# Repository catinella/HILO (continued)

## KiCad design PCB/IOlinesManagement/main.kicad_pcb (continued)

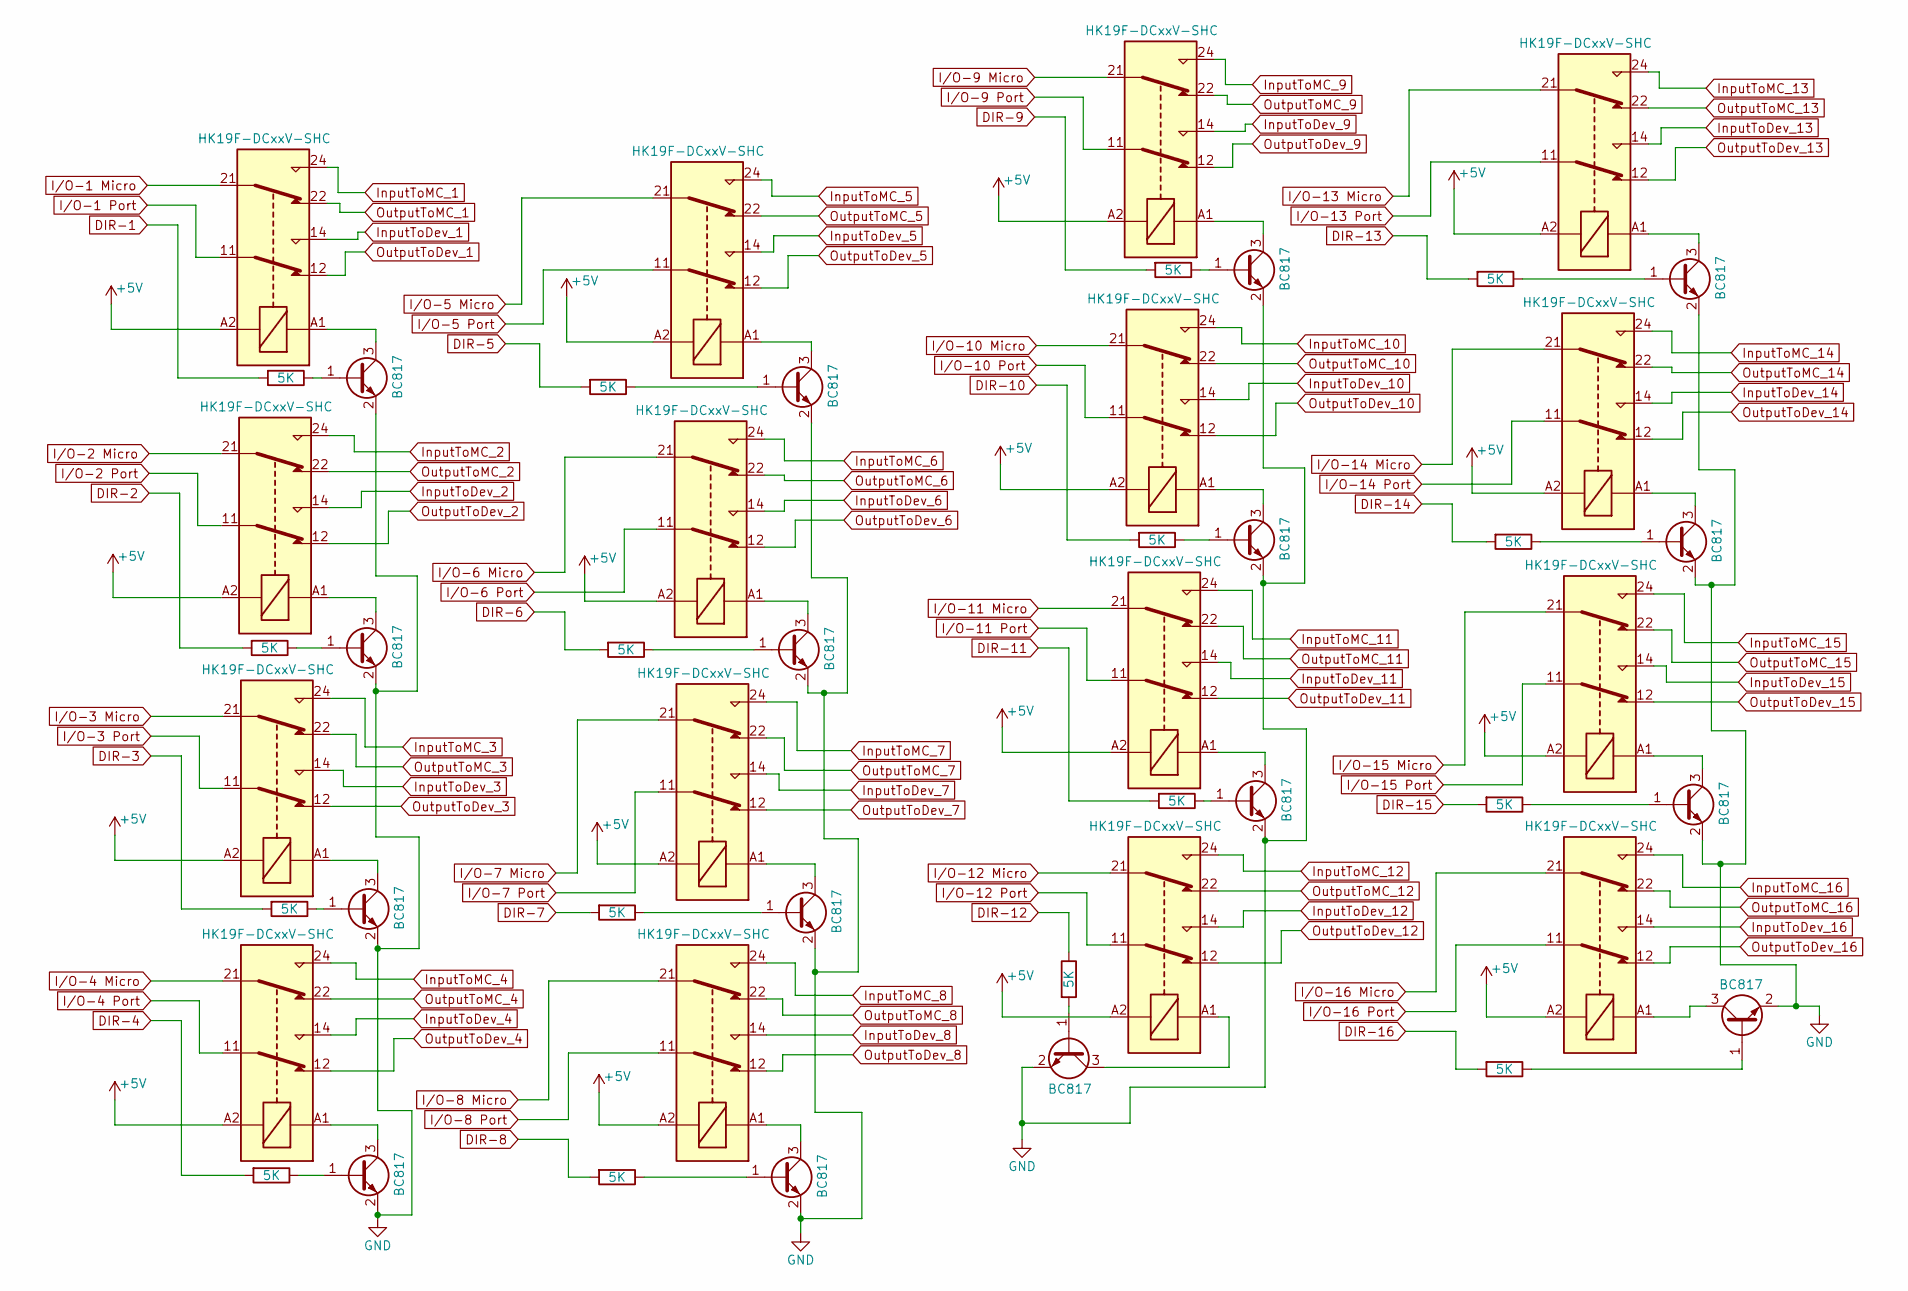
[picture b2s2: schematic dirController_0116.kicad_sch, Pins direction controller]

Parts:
K1, K2, K3, K4, K5, K6, K7, K8, K9, K10, K11, K12, K13, K14, K15, K16: HK19F-DCxxV-SHC; Relay_DPDT_Finder_30.22
Q1, Q2, Q3, Q4, Q5, Q6, Q7, Q8, Q9, Q10, Q11, Q12, Q13, Q14, Q15, Q16: BC817; SOT-23
R1, R2, R3, R4, R5, R6, R7, R8, R9, R10, R11, R12, R13, R14, R15, R16: 5K; R_1206_3216Metric

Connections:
+5V: K1.A2, K2.A2, K3.A2, K4.A2, K5.A2, K6.A2, K7.A2, K8.A2, K9.A2, K10.A2, K11.A2, K12.A2, K13.A2, K14.A2, K15.A2, K16.A2; also elsewhere on the board
DIR-1: R3.2; also elsewhere on the board
DIR-2: R1.2; also elsewhere on the board
DIR-3: R4.2; also elsewhere on the board
DIR-4: R2.2; also elsewhere on the board
DIR-5: R5.2; also elsewhere on the board
DIR-6: R8.2; also elsewhere on the board
DIR-7: R6.2; also elsewhere on the board
DIR-8: R7.2; also elsewhere on the board
DIR-9: R11.2; also elsewhere on the board
DIR-10: R10.2; also elsewhere on the board
DIR-11: R12.2; also elsewhere on the board
DIR-12: R9.1; also elsewhere on the board
DIR-13: R13.2; also elsewhere on the board
DIR-14: R16.2; also elsewhere on the board
DIR-15: R14.2; also elsewhere on the board
DIR-16: R15.2; also elsewhere on the board
GND: Q1.2 (E), Q2.2 (E), Q3.2 (E), Q4.2 (E), Q5.2 (E), Q6.2 (E), Q7.2 (E), Q8.2 (E), Q9.2 (E), Q10.2 (E), Q11.2 (E), Q12.2 (E), Q13.2 (E), Q14.2 (E), Q15.2 (E), Q16.2 (E); also elsewhere on the board
InputToDev_1: K1.14; also elsewhere on the board
InputToDev_2: K2.14; also elsewhere on the board
InputToDev_3: K3.14; also elsewhere on the board
InputToDev_4: K4.14; also elsewhere on the board
InputToDev_5: K5.14; also elsewhere on the board
InputToDev_6: K6.14; also elsewhere on the board
InputToDev_7: K7.14; also elsewhere on the board
InputToDev_8: K8.14; also elsewhere on the board
InputToDev_9: K9.14; also elsewhere on the board
InputToDev_10: K10.14; also elsewhere on the board
InputToDev_11: K11.14; also elsewhere on the board
InputToDev_12: K12.14; also elsewhere on the board
InputToDev_13: K13.14; also elsewhere on the board
InputToDev_14: K14.14; also elsewhere on the board
InputToDev_15: K15.14; also elsewhere on the board
InputToDev_16: K16.14; also elsewhere on the board
InputToMC_1: K1.24; also elsewhere on the board
InputToMC_2: K2.24; also elsewhere on the board
InputToMC_3: K3.24; also elsewhere on the board
InputToMC_4: K4.24; also elsewhere on the board
InputToMC_5: K5.24; also elsewhere on the board
InputToMC_6: K6.24; also elsewhere on the board
InputToMC_7: K7.24; also elsewhere on the board
InputToMC_8: K8.24; also elsewhere on the board
InputToMC_9: K9.24; also elsewhere on the board
InputToMC_10: K10.24; also elsewhere on the board
InputToMC_11: K11.24; also elsewhere on the board
InputToMC_12: K12.24; also elsewhere on the board
InputToMC_13: K13.24; also elsewhere on the board
InputToMC_14: K14.24; also elsewhere on the board
InputToMC_15: K15.24; also elsewhere on the board
InputToMC_16: K16.24; also elsewhere on the board
I/O-1 Micro: K1.21; also elsewhere on the board
I/O-1 Port: K1.11; also elsewhere on the board
I/O-2 Micro: K2.21; also elsewhere on the board
I/O-2 Port: K2.11; also elsewhere on the board
I/O-3 Micro: K3.21; also elsewhere on the board
I/O-3 Port: K3.11; also elsewhere on the board
I/O-4 Micro: K4.21; also elsewhere on the board
I/O-4 Port: K4.11; also elsewhere on the board
I/O-5 Micro: K5.21; also elsewhere on the board
I/O-5 Port: K5.11; also elsewhere on the board
I/O-6 Micro: K6.21; also elsewhere on the board
I/O-6 Port: K6.11; also elsewhere on the board
I/O-7 Micro: K7.21; also elsewhere on the board
I/O-7 Port: K7.11; also elsewhere on the board
I/O-8 Micro: K8.21; also elsewhere on the board
I/O-8 Port: K8.11; also elsewhere on the board
I/O-9 Micro: K9.21; also elsewhere on the board
I/O-9 Port: K9.11; also elsewhere on the board
I/O-10 Micro: K10.21; also elsewhere on the board
I/O-10 Port: K10.11; also elsewhere on the board
I/O-11 Micro: K11.21; also elsewhere on the board
I/O-11 Port: K11.11; also elsewhere on the board
I/O-12 Micro: K12.21; also elsewhere on the board
I/O-12 Port: K12.11; also elsewhere on the board
I/O-13 Micro: K13.21; also elsewhere on the board
I/O-13 Port: K13.11; also elsewhere on the board
I/O-14 Micro: K14.21; also elsewhere on the board
I/O-14 Port: K14.11; also elsewhere on the board
I/O-15 Micro: K15.21; also elsewhere on the board
I/O-15 Port: K15.11; also elsewhere on the board
I/O-16 Micro: K16.21; also elsewhere on the board
I/O-16 Port: K16.11; also elsewhere on the board
unnamed: Q1.1 (B), R3.1
unnamed: K1.A1, Q1.3 (C)
unnamed: Q2.1 (B), R1.1
unnamed: K2.A1, Q2.3 (C)
unnamed: Q3.1 (B), R4.1
unnamed: K3.A1, Q3.3 (C)
unnamed: Q4.1 (B), R2.1
unnamed: K4.A1, Q4.3 (C)
unnamed: Q5.1 (B), R7.1
unnamed: K8.A1, Q5.3 (C)
unnamed: Q6.1 (B), R8.1
unnamed: K6.A1, Q6.3 (C)
unnamed: Q7.1 (B), R5.1
unnamed: K5.A1, Q7.3 (C)
unnamed: Q8.1 (B), R6.1
unnamed: K7.A1, Q8.3 (C)
unnamed: Q9.1 (B), R9.2
unnamed: K12.A1, Q9.3 (C)
unnamed: Q10.1 (B), R11.1
unnamed: K9.A1, Q10.3 (C)
unnamed: Q11.1 (B), R10.1
unnamed: K10.A1, Q11.3 (C)
unnamed: Q12.1 (B), R12.1
unnamed: K11.A1, Q12.3 (C)
unnamed: Q13.1 (B), R16.1
unnamed: K14.A1, Q13.3 (C)
unnamed: Q14.1 (B), R13.1
unnamed: K13.A1, Q14.3 (C)
unnamed: Q15.1 (B), R14.1
unnamed: K15.A1, Q15.3 (C)
unnamed: Q16.1 (B), R15.1
unnamed: K16.A1, Q16.3 (C)
OutputToDev_1: K1.12; also elsewhere on the board
OutputToDev_2: K2.12; also elsewhere on the board
OutputToDev_3: K3.12; also elsewhere on the board
OutputToDev_4: K4.12; also elsewhere on the board
OutputToDev_5: K5.12; also elsewhere on the board
OutputToDev_6: K6.12; also elsewhere on the board
OutputToDev_7: K7.12; also elsewhere on the board
OutputToDev_8: K8.12; also elsewhere on the board
OutputToDev_9: K9.12; also elsewhere on the board
OutputToDev_10: K10.12; also elsewhere on the board
OutputToDev_11: K11.12; also elsewhere on the board
OutputToDev_12: K12.12; also elsewhere on the board
OutputToDev_13: K13.12; also elsewhere on the board
OutputToDev_14: K14.12; also elsewhere on the board
OutputToDev_15: K15.12; also elsewhere on the board
OutputToDev_16: K16.12; also elsewhere on the board
OutputToMC_1: K1.22; also elsewhere on the board
OutputToMC_2: K2.22; also elsewhere on the board
OutputToMC_3: K3.22; also elsewhere on the board
OutputToMC_4: K4.22; also elsewhere on the board
OutputToMC_5: K5.22; also elsewhere on the board
OutputToMC_6: K6.22; also elsewhere on the board
OutputToMC_7: K7.22; also elsewhere on the board
OutputToMC_8: K8.22; also elsewhere on the board
OutputToMC_9: K9.22; also elsewhere on the board
OutputToMC_10: K10.22; also elsewhere on the board
OutputToMC_11: K11.22; also elsewhere on the board
OutputToMC_12: K12.22; also elsewhere on the board
OutputToMC_13: K13.22; also elsewhere on the board
OutputToMC_14: K14.22; also elsewhere on the board
OutputToMC_15: K15.22; also elsewhere on the board
OutputToMC_16: K16.22; also elsewhere on the board

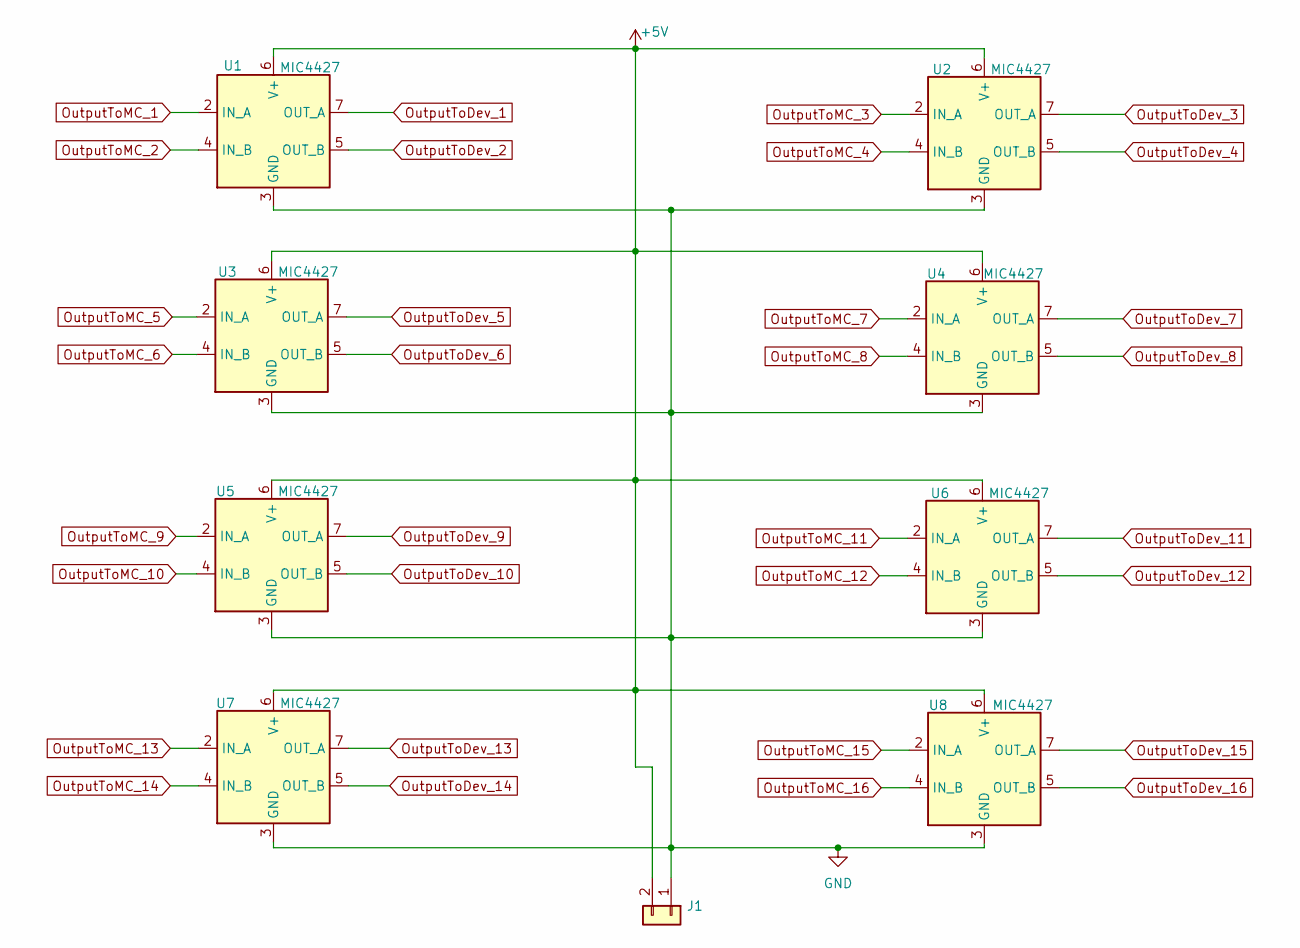
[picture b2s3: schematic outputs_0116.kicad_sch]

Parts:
J1: Conn_01x02; PinHeader_1x02_P2.54mm_Vertical
U1, U2, U3, U4, U5, U6, U7, U8: MIC4427; MSOP-8_3x3mm_P0.65mm

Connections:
+5V: J1.2, U1.6 (V+), U2.6 (V+), U3.6 (V+), U4.6 (V+), U5.6 (V+), U6.6 (V+), U7.6 (V+), U8.6 (V+); also elsewhere on the board
GND: J1.1, U1.3 (GND), U2.3 (GND), U3.3 (GND), U4.3 (GND), U5.3 (GND), U6.3 (GND), U7.3 (GND), U8.3 (GND); also elsewhere on the board
OutputToDev_1: U1.7 (OUT_A); also elsewhere on the board
OutputToDev_2: U1.5 (OUT_B); also elsewhere on the board
OutputToDev_3: U2.7 (OUT_A); also elsewhere on the board
OutputToDev_4: U2.5 (OUT_B); also elsewhere on the board
OutputToDev_5: U3.7 (OUT_A); also elsewhere on the board
OutputToDev_6: U3.5 (OUT_B); also elsewhere on the board
OutputToDev_7: U4.7 (OUT_A); also elsewhere on the board
OutputToDev_8: U4.5 (OUT_B); also elsewhere on the board
OutputToDev_9: U5.7 (OUT_A); also elsewhere on the board
OutputToDev_10: U5.5 (OUT_B); also elsewhere on the board
OutputToDev_11: U6.7 (OUT_A); also elsewhere on the board
OutputToDev_12: U6.5 (OUT_B); also elsewhere on the board
OutputToDev_13: U7.7 (OUT_A); also elsewhere on the board
OutputToDev_14: U7.5 (OUT_B); also elsewhere on the board
OutputToDev_15: U8.7 (OUT_A); also elsewhere on the board
OutputToDev_16: U8.5 (OUT_B); also elsewhere on the board
OutputToMC_1: U1.2 (IN_A); also elsewhere on the board
OutputToMC_2: U1.4 (IN_B); also elsewhere on the board
OutputToMC_3: U2.2 (IN_A); also elsewhere on the board
OutputToMC_4: U2.4 (IN_B); also elsewhere on the board
OutputToMC_5: U3.2 (IN_A); also elsewhere on the board
OutputToMC_6: U3.4 (IN_B); also elsewhere on the board
OutputToMC_7: U4.2 (IN_A); also elsewhere on the board
OutputToMC_8: U4.4 (IN_B); also elsewhere on the board
OutputToMC_9: U5.2 (IN_A); also elsewhere on the board
OutputToMC_10: U5.4 (IN_B); also elsewhere on the board
OutputToMC_11: U6.2 (IN_A); also elsewhere on the board
OutputToMC_12: U6.4 (IN_B); also elsewhere on the board
OutputToMC_13: U7.2 (IN_A); also elsewhere on the board
OutputToMC_14: U7.4 (IN_B); also elsewhere on the board
OutputToMC_15: U8.2 (IN_A); also elsewhere on the board
OutputToMC_16: U8.4 (IN_B); also elsewhere on the board

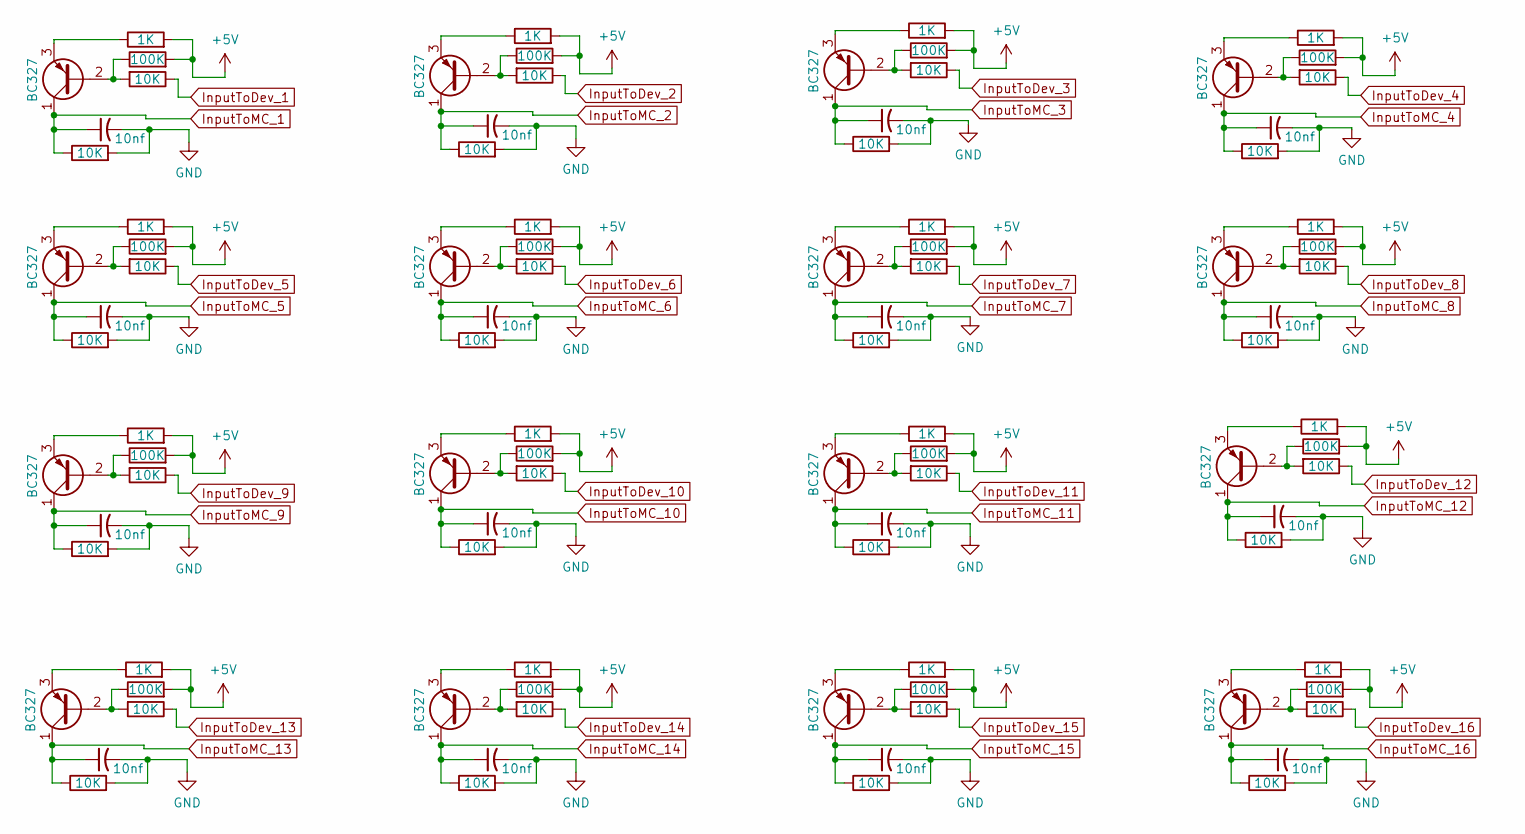
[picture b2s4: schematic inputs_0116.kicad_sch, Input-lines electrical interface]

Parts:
C1, C2, C3, C4, C5, C6, C7, C8, C9, C10, C11, C12, C13, C14, C15, C16: 10nf; C_Disc_D4.3mm_W1.9mm_P5.00mm
Q25, Q34, Q51, Q52, Q53, Q54, Q55, Q56, Q57, Q58, Q59, Q60, Q61, Q62, Q63, Q64: BC327; TO-92_Inline_Wide
R17, R54, R82, R112, R113, R114, R117, R120, R125, R128, R140, R146, R147, R148, R151, R156: 1K; R_1206_3216Metric
R40, R56, R65, R84, R105, R106, R107, R108, R109, R110, R111, R116, R119, R122, R124, R127, R130, R132, R133, R134, R135, R136, R137, R138, R139, R142, R145, R150, R153, R155, R158, R160: 10K; R_1206_3216Metric
R55, R83, R115, R118, R121, R123, R126, R129, R131, R141, R144, R149, R152, R154, R157, R159: 100K; R_1206_3216Metric

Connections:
+5V: R17.2, R54.2, R55.2, R82.2, R83.2, R112.2, R113.2, R114.2, R115.2, R117.2, R118.2, R120.2, R121.2, R123.2, R125.2, R126.2, R128.2, R129.2, R131.2, R140.2, R141.2, R144.2, R146.2, R147.2, R148.2, R149.2, R151.2, R152.2, R154.2, R156.2, R157.2, R159.2; also elsewhere on the board
GND: C1.2, C2.2, C3.2, C4.2, C5.2, C6.2, C7.2, C8.2, C9.2, C10.2, C11.2, C12.2, C13.2, C14.2, C15.2, C16.2, R40.2, R65.2, R105.2, R106.2, R107.2, R108.2, R109.2, R110.2, R111.2, R133.2, R134.2, R135.2, R136.2, R137.2, R138.2, R139.2; also elsewhere on the board
InputToDev_1: R56.1; also elsewhere on the board
InputToDev_2: R84.1; also elsewhere on the board
InputToDev_3: R142.1; also elsewhere on the board
InputToDev_4: R132.1; also elsewhere on the board
InputToDev_5: R122.1; also elsewhere on the board
InputToDev_6: R145.1; also elsewhere on the board
InputToDev_7: R153.1; also elsewhere on the board
InputToDev_8: R116.1; also elsewhere on the board
InputToDev_9: R124.1; also elsewhere on the board
InputToDev_10: R119.1; also elsewhere on the board
InputToDev_11: R130.1; also elsewhere on the board
InputToDev_12: R127.1; also elsewhere on the board
InputToDev_13: R155.1; also elsewhere on the board
InputToDev_14: R150.1; also elsewhere on the board
InputToDev_15: R160.1; also elsewhere on the board
InputToDev_16: R158.1; also elsewhere on the board
InputToMC_1: C1.1, Q25.1 (C), R40.1; also elsewhere on the board
InputToMC_2: C2.1, Q34.1 (C), R65.1; also elsewhere on the board
InputToMC_3: C10.1, Q58.1 (C), R133.1; also elsewhere on the board
InputToMC_4: C9.1, Q57.1 (C), R111.1; also elsewhere on the board
InputToMC_5: C5.1, Q53.1 (C), R107.1; also elsewhere on the board
InputToMC_6: C11.1, Q59.1 (C), R134.1; also elsewhere on the board
InputToMC_7: C13.1, Q61.1 (C), R136.1; also elsewhere on the board
InputToMC_8: C3.1, Q51.1 (C), R105.1; also elsewhere on the board
InputToMC_9: C6.1, Q54.1 (C), R108.1; also elsewhere on the board
InputToMC_10: C4.1, Q52.1 (C), R106.1; also elsewhere on the board
InputToMC_11: C8.1, Q56.1 (C), R110.1; also elsewhere on the board
InputToMC_12: C7.1, Q55.1 (C), R109.1; also elsewhere on the board
InputToMC_13: C14.1, Q62.1 (C), R137.1; also elsewhere on the board
InputToMC_14: C12.1, Q60.1 (C), R135.1; also elsewhere on the board
InputToMC_15: C16.1, Q64.1 (C), R139.1; also elsewhere on the board
InputToMC_16: C15.1, Q63.1 (C), R138.1; also elsewhere on the board
unnamed: Q25.2 (B), R55.1, R56.2
unnamed: Q25.3 (E), R54.1
unnamed: Q34.2 (B), R83.1, R84.2
unnamed: Q34.3 (E), R82.1
unnamed: Q51.2 (B), R115.1, R116.2
unnamed: Q51.3 (E), R112.1
unnamed: Q52.2 (B), R118.1, R119.2
unnamed: Q52.3 (E), R113.1
unnamed: Q53.2 (B), R121.1, R122.2
unnamed: Q53.3 (E), R114.1
unnamed: Q54.2 (B), R123.1, R124.2
unnamed: Q54.3 (E), R117.1
unnamed: Q55.2 (B), R126.1, R127.2
unnamed: Q55.3 (E), R120.1
unnamed: Q56.2 (B), R129.1, R130.2
unnamed: Q56.3 (E), R125.1
unnamed: Q57.2 (B), R131.1, R132.2
unnamed: Q57.3 (E), R128.1
unnamed: Q58.2 (B), R141.1, R142.2
unnamed: Q58.3 (E), R140.1
unnamed: Q59.2 (B), R144.1, R145.2
unnamed: Q59.3 (E), R17.1
unnamed: Q60.2 (B), R149.1, R150.2
unnamed: Q60.3 (E), R146.1
unnamed: Q61.2 (B), R152.1, R153.2
unnamed: Q61.3 (E), R147.1
unnamed: Q62.2 (B), R154.1, R155.2
unnamed: Q62.3 (E), R148.1
unnamed: Q63.2 (B), R157.1, R158.2
unnamed: Q63.3 (E), R151.1
unnamed: Q64.2 (B), R159.1, R160.2
unnamed: Q64.3 (E), R156.1

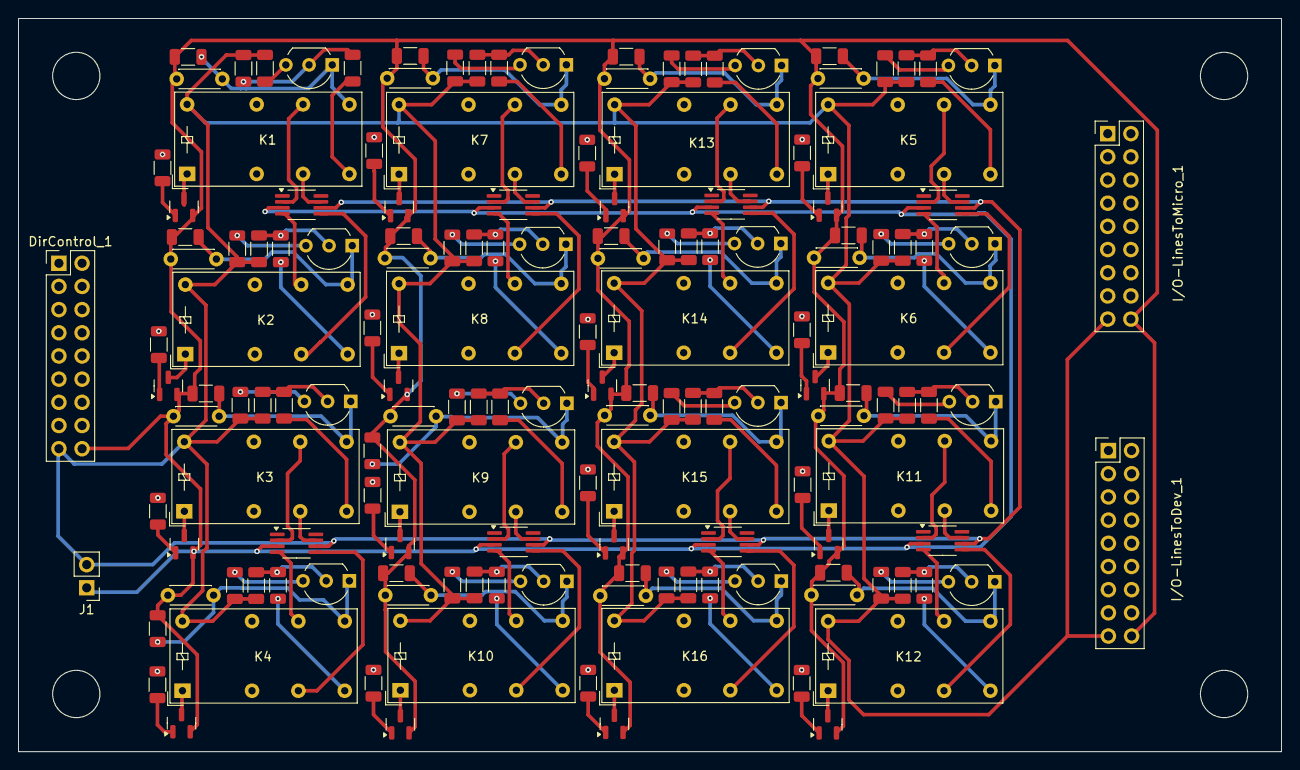
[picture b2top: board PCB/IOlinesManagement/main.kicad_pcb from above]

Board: 4 copper layers, 138.4 x 80.3 mm, 156 parts (0 on the bottom side), 178 nets.

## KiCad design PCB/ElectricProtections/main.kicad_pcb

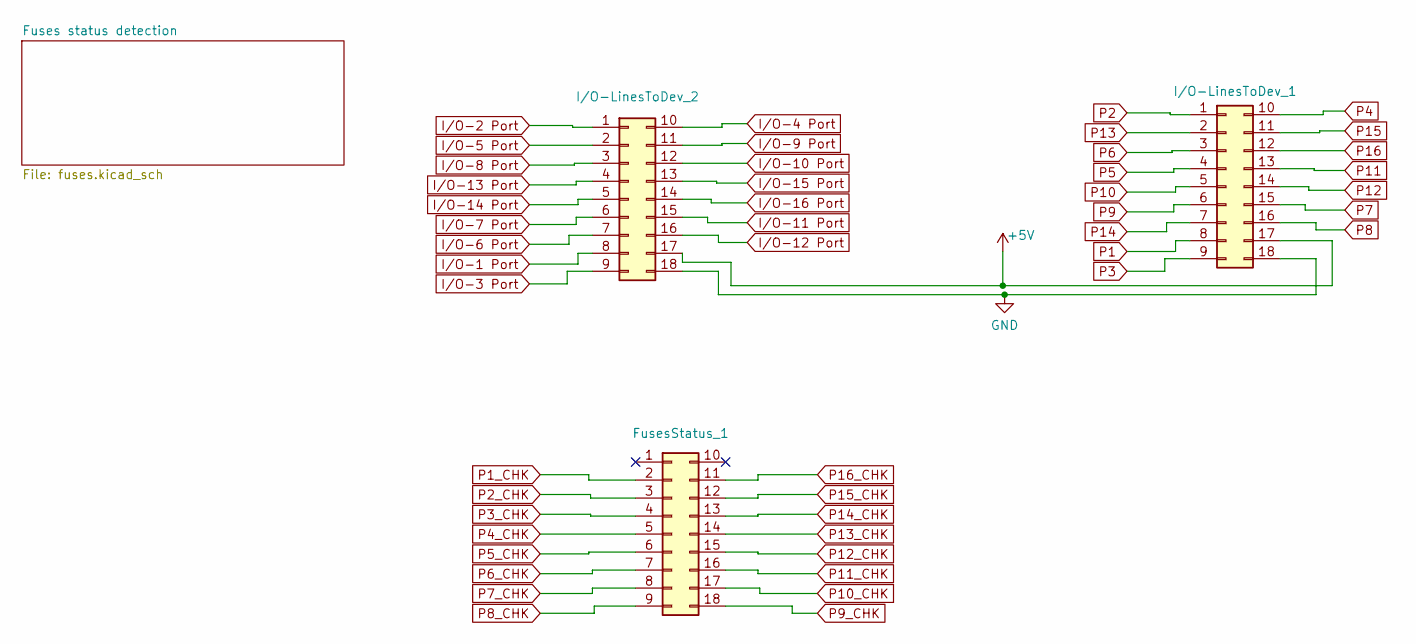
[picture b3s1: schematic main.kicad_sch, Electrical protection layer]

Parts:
FusesStatus_1: Conn_02x09_Top_Bottom; PinHeader_2x09_P2.54mm_Vertical
I/O-LinesToDev_1, I/O-LinesToDev_2: Conn_02x09_Top_Bottom; PinHeader_2x09_P2.54mm_Vertical

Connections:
+5V: I/O-LinesToDev_1.17, I/O-LinesToDev_2.17; also elsewhere on the board
GND: I/O-LinesToDev_1.18, I/O-LinesToDev_2.18; also elsewhere on the board
I/O-1 Port: I/O-LinesToDev_2.8; also elsewhere on the board
I/O-2 Port: I/O-LinesToDev_2.1; also elsewhere on the board
I/O-3 Port: I/O-LinesToDev_2.9; also elsewhere on the board
I/O-4 Port: I/O-LinesToDev_2.10; also elsewhere on the board
I/O-5 Port: I/O-LinesToDev_2.2; also elsewhere on the board
I/O-6 Port: I/O-LinesToDev_2.7; also elsewhere on the board
I/O-7 Port: I/O-LinesToDev_2.6; also elsewhere on the board
I/O-8 Port: I/O-LinesToDev_2.3; also elsewhere on the board
I/O-9 Port: I/O-LinesToDev_2.11; also elsewhere on the board
I/O-10 Port: I/O-LinesToDev_2.12; also elsewhere on the board
I/O-11 Port: I/O-LinesToDev_2.15; also elsewhere on the board
I/O-12 Port: I/O-LinesToDev_2.16; also elsewhere on the board
I/O-13 Port: I/O-LinesToDev_2.4; also elsewhere on the board
I/O-14 Port: I/O-LinesToDev_2.5; also elsewhere on the board
I/O-15 Port: I/O-LinesToDev_2.13; also elsewhere on the board
I/O-16 Port: I/O-LinesToDev_2.14; also elsewhere on the board
P1: I/O-LinesToDev_1.8; also elsewhere on the board
P1_CHK: FusesStatus_1.2; also elsewhere on the board
P2: I/O-LinesToDev_1.1; also elsewhere on the board
P2_CHK: FusesStatus_1.3; also elsewhere on the board
P3: I/O-LinesToDev_1.9; also elsewhere on the board
P3_CHK: FusesStatus_1.4; also elsewhere on the board
P4: I/O-LinesToDev_1.10; also elsewhere on the board
P4_CHK: FusesStatus_1.5; also elsewhere on the board
P5: I/O-LinesToDev_1.4; also elsewhere on the board
P5_CHK: FusesStatus_1.6; also elsewhere on the board
P6: I/O-LinesToDev_1.3; also elsewhere on the board
P6_CHK: FusesStatus_1.7; also elsewhere on the board
P7: I/O-LinesToDev_1.15; also elsewhere on the board
P7_CHK: FusesStatus_1.8; also elsewhere on the board
P8: I/O-LinesToDev_1.16; also elsewhere on the board
P8_CHK: FusesStatus_1.9; also elsewhere on the board
P9: I/O-LinesToDev_1.6; also elsewhere on the board
P9_CHK: FusesStatus_1.18; also elsewhere on the board
P10: I/O-LinesToDev_1.5; also elsewhere on the board
P10_CHK: FusesStatus_1.17; also elsewhere on the board
P11: I/O-LinesToDev_1.13; also elsewhere on the board
P11_CHK: FusesStatus_1.16; also elsewhere on the board
P12: I/O-LinesToDev_1.14; also elsewhere on the board
P12_CHK: FusesStatus_1.15; also elsewhere on the board
P13: I/O-LinesToDev_1.2; also elsewhere on the board
P13_CHK: FusesStatus_1.14; also elsewhere on the board
P14: I/O-LinesToDev_1.7; also elsewhere on the board
P14_CHK: FusesStatus_1.13; also elsewhere on the board
P15: I/O-LinesToDev_1.11; also elsewhere on the board
P15_CHK: FusesStatus_1.12; also elsewhere on the board
P16: I/O-LinesToDev_1.12; also elsewhere on the board
P16_CHK: FusesStatus_1.11; also elsewhere on the board

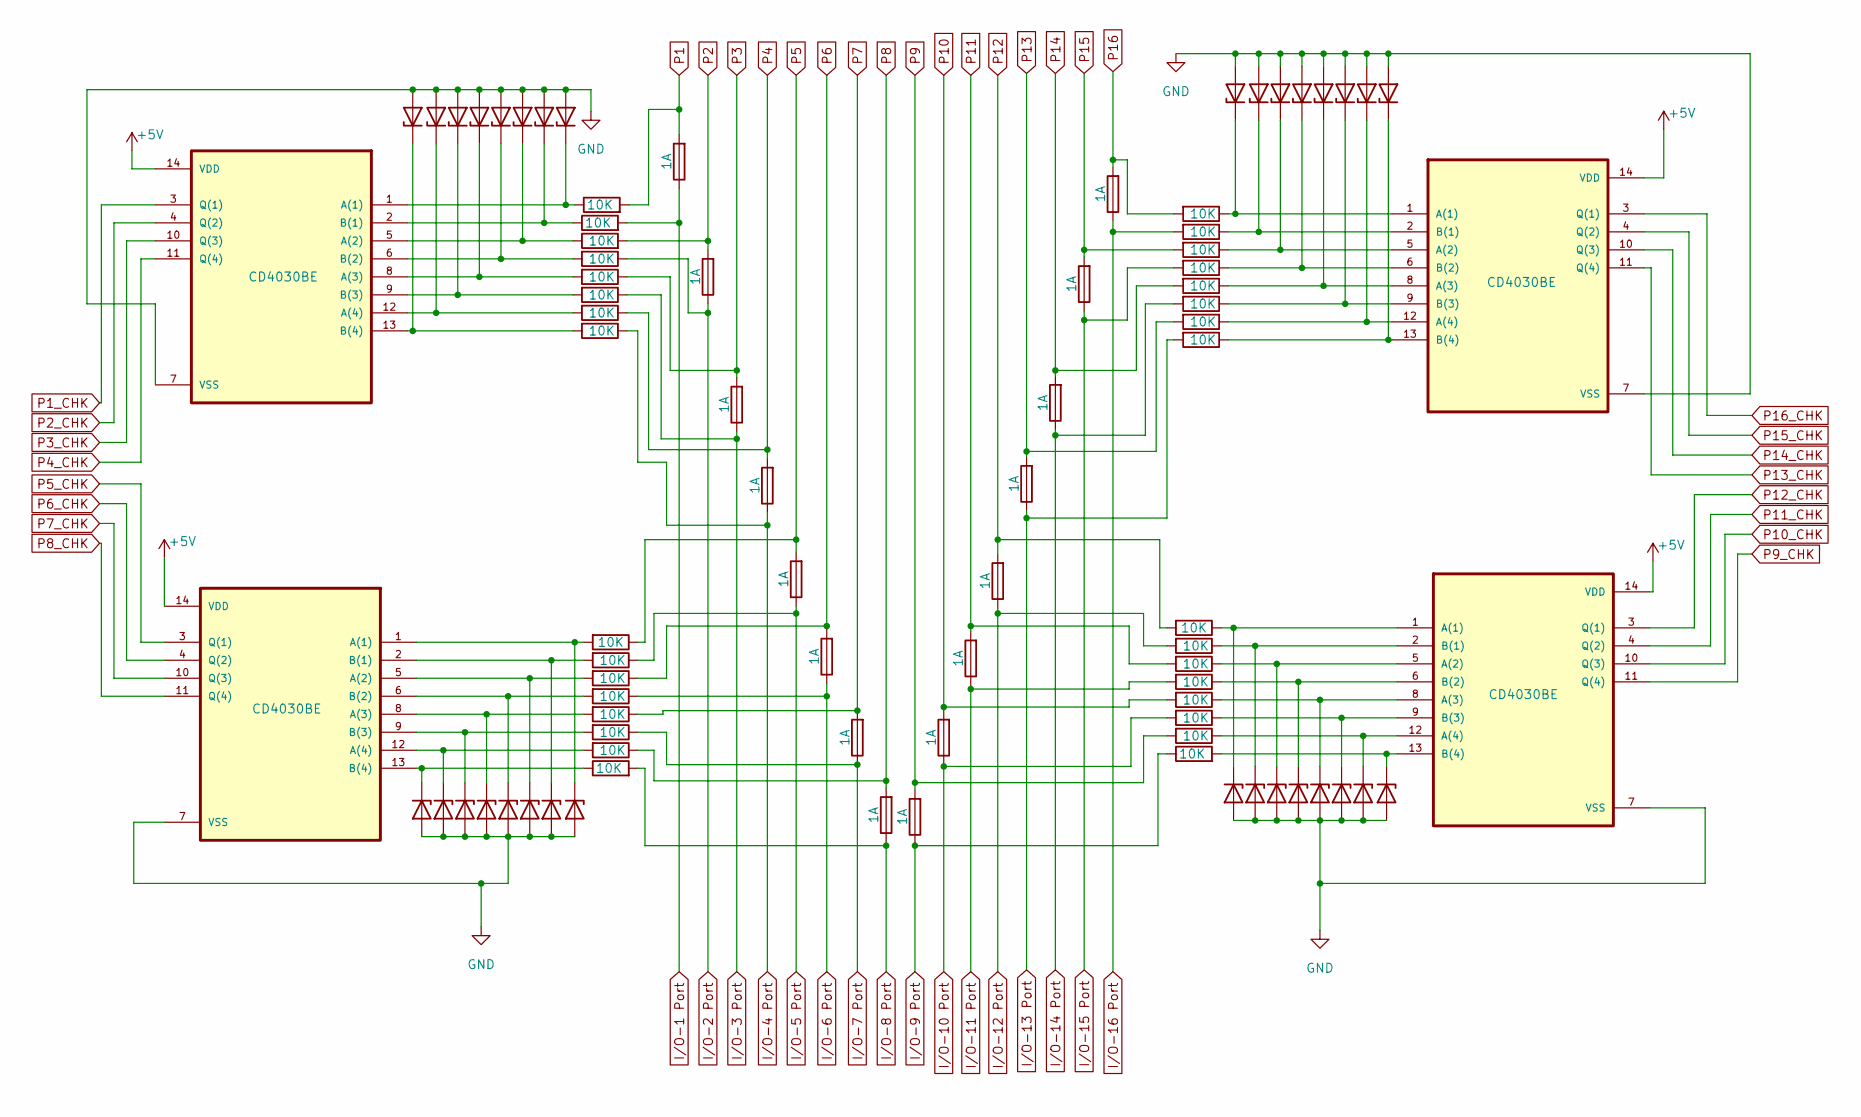
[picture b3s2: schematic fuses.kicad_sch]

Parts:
D1, D2, D3, D4, D5, D6, D7, D8, D9, D10, D11, D12, D13, D14, D15, D16, D17, D18, D19, D20, D21, D22, D23, D24, D25, D26, D27, D28, D29, D30, D31, D32: 5V; D_1206_3216Metric
F1, F2, F3, F4, F5, F6, F7, F8, F9, F10, F11, F12, F13, F14, F15, F16: 1A; Fuseholder_Cylinder-5x20mm_Schurter_0031_8201_Horizontal_Op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
R1, R2, R3, R4, R5, R6, R7, R8, R9, R10, R11, R12, R13, R14, R15, R16, R17, R18, R19, R20, R21, R22, R23, R24, R25, R26, R27, R28, R29, R30, R31, R32: 10K; R_1206_3216Metric
U1, U2, U3, U4: CD4030BE; DIP-14_W7.62mm_LongPads

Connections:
+5V: U1.14 (VDD), U2.14 (VDD), U3.14 (VDD), U4.14 (VDD); also elsewhere on the board
GND: D1.2 (A), D2.2 (A), D3.2 (A), D4.2 (A), D5.2 (A), D6.2 (A), D7.2 (A), D8.2 (A), D9.2 (A), D10.2 (A), D11.2 (A), D12.2 (A), D13.2 (A), D14.2 (A), D15.2 (A), D16.2 (A), D17.2 (A), D18.2 (A), D19.2 (A), D20.2 (A), D21.2 (A), D22.2 (A), D23.2 (A), D24.2 (A), D25.2 (A), D26.2 (A), D27.2 (A), D28.2 (A), D29.2 (A), D30.2 (A), D31.2 (A), D32.2 (A), U1.7 (VSS), U2.7 (VSS), U3.7 (VSS), U4.7 (VSS); also elsewhere on the board
I/O-1 Port: F1.1, R23.2; also elsewhere on the board
I/O-2 Port: F2.1, R21.1; also elsewhere on the board
I/O-3 Port: F3.1, R19.1; also elsewhere on the board
I/O-4 Port: F4.1, R17.1; also elsewhere on the board
I/O-5 Port: F5.1, R26.1; also elsewhere on the board
I/O-6 Port: F6.1, R28.1; also elsewhere on the board
I/O-7 Port: F7.1, R30.1; also elsewhere on the board
I/O-8 Port: F8.1, R32.2; also elsewhere on the board
I/O-9 Port: F9.1, R16.1; also elsewhere on the board
I/O-10 Port: F10.1, R14.2; also elsewhere on the board
I/O-11 Port: F11.1, R12.2; also elsewhere on the board
I/O-12 Port: F12.1, R10.2; also elsewhere on the board
I/O-13 Port: F13.1, R8.2; also elsewhere on the board
I/O-14 Port: F14.1, R6.2; also elsewhere on the board
I/O-15 Port: F15.1, R2.2; also elsewhere on the board
I/O-16 Port: F16.1, R4.2; also elsewhere on the board
unnamed: D1.1 (K), R23.1, U1.2 (B(1))
unnamed: D2.1 (K), R24.1, U1.5 (A(2))
unnamed: D3.1 (K), R21.2, U1.6 (B(2))
unnamed: D4.1 (K), R20.2, U1.8 (A(3))
unnamed: D5.1 (K), R19.2, U1.9 (B(3))
unnamed: D6.1 (K), R18.2, U1.12 (A(4))
unnamed: D7.1 (K), R17.2, U1.13 (B(4))
unnamed: D8.1 (K), R22.1, U1.1 (A(1))
unnamed: D9.1 (K), R1.1, U4.1 (A(1))
unnamed: D10.1 (K), R4.1, U4.2 (B(1))
unnamed: D11.1 (K), R3.1, U4.5 (A(2))
unnamed: D12.1 (K), R2.1, U4.6 (B(2))
unnamed: D13.1 (K), R7.1, U4.8 (A(3))
unnamed: D14.1 (K), R6.1, U4.9 (B(3))
unnamed: D15.1 (K), R5.1, U4.12 (A(4))
unnamed: D16.1 (K), R8.1, U4.13 (B(4))
unnamed: D17.1 (K), R16.2, U3.13 (B(4))
unnamed: D18.1 (K), R15.1, U3.12 (A(4))
unnamed: D19.1 (K), R14.1, U3.9 (B(3))
unnamed: D20.1 (K), R13.1, U3.8 (A(3))
unnamed: D21.1 (K), R12.1, U3.6 (B(2))
unnamed: D22.1 (K), R11.1, U3.5 (A(2))
unnamed: D23.1 (K), R10.1, U3.2 (B(1))
unnamed: D24.1 (K), R9.1, U3.1 (A(1))
unnamed: D25.1 (K), R32.1, U2.13 (B(4))
unnamed: D26.1 (K), R31.2, U2.12 (A(4))
unnamed: D27.1 (K), R30.2, U2.9 (B(3))
unnamed: D28.1 (K), R29.2, U2.8 (A(3))
unnamed: D29.1 (K), R28.2, U2.6 (B(2))
unnamed: D30.1 (K), R27.2, U2.5 (A(2))
unnamed: D31.1 (K), R26.2, U2.2 (B(1))
unnamed: D32.1 (K), R25.2, U2.1 (A(1))
P1: F1.2, R22.2; also elsewhere on the board
P1_CHK: U1.3 (Q(1)); also elsewhere on the board
P2: F2.2, R24.2; also elsewhere on the board
P2_CHK: U1.4 (Q(2)); also elsewhere on the board
P3: F3.2, R20.1; also elsewhere on the board
P3_CHK: U1.10 (Q(3)); also elsewhere on the board
P4: F4.2, R18.1; also elsewhere on the board
P4_CHK: U1.11 (Q(4)); also elsewhere on the board
P5: F5.2, R25.1; also elsewhere on the board
P5_CHK: U2.3 (Q(1)); also elsewhere on the board
P6: F6.2, R27.1; also elsewhere on the board
P6_CHK: U2.4 (Q(2)); also elsewhere on the board
P7: F7.2, R29.1; also elsewhere on the board
P7_CHK: U2.10 (Q(3)); also elsewhere on the board
P8: F8.2, R31.1; also elsewhere on the board
P8_CHK: U2.11 (Q(4)); also elsewhere on the board
P9: F9.2, R15.2; also elsewhere on the board
P9_CHK: U3.11 (Q(4)); also elsewhere on the board
P10: F10.2, R13.2; also elsewhere on the board
P10_CHK: U3.10 (Q(3)); also elsewhere on the board
P11: F11.2, R11.2; also elsewhere on the board
P11_CHK: U3.4 (Q(2)); also elsewhere on the board
P12: F12.2, R9.2; also elsewhere on the board
P12_CHK: U3.3 (Q(1)); also elsewhere on the board
P13: F13.2, R5.2; also elsewhere on the board
P13_CHK: U4.11 (Q(4)); also elsewhere on the board
P14: F14.2, R7.2; also elsewhere on the board
P14_CHK: U4.10 (Q(3)); also elsewhere on the board
P15: F15.2, R3.2; also elsewhere on the board
P15_CHK: U4.4 (Q(2)); also elsewhere on the board
P16: F16.2, R1.2; also elsewhere on the board
P16_CHK: U4.3 (Q(1)); also elsewhere on the board
